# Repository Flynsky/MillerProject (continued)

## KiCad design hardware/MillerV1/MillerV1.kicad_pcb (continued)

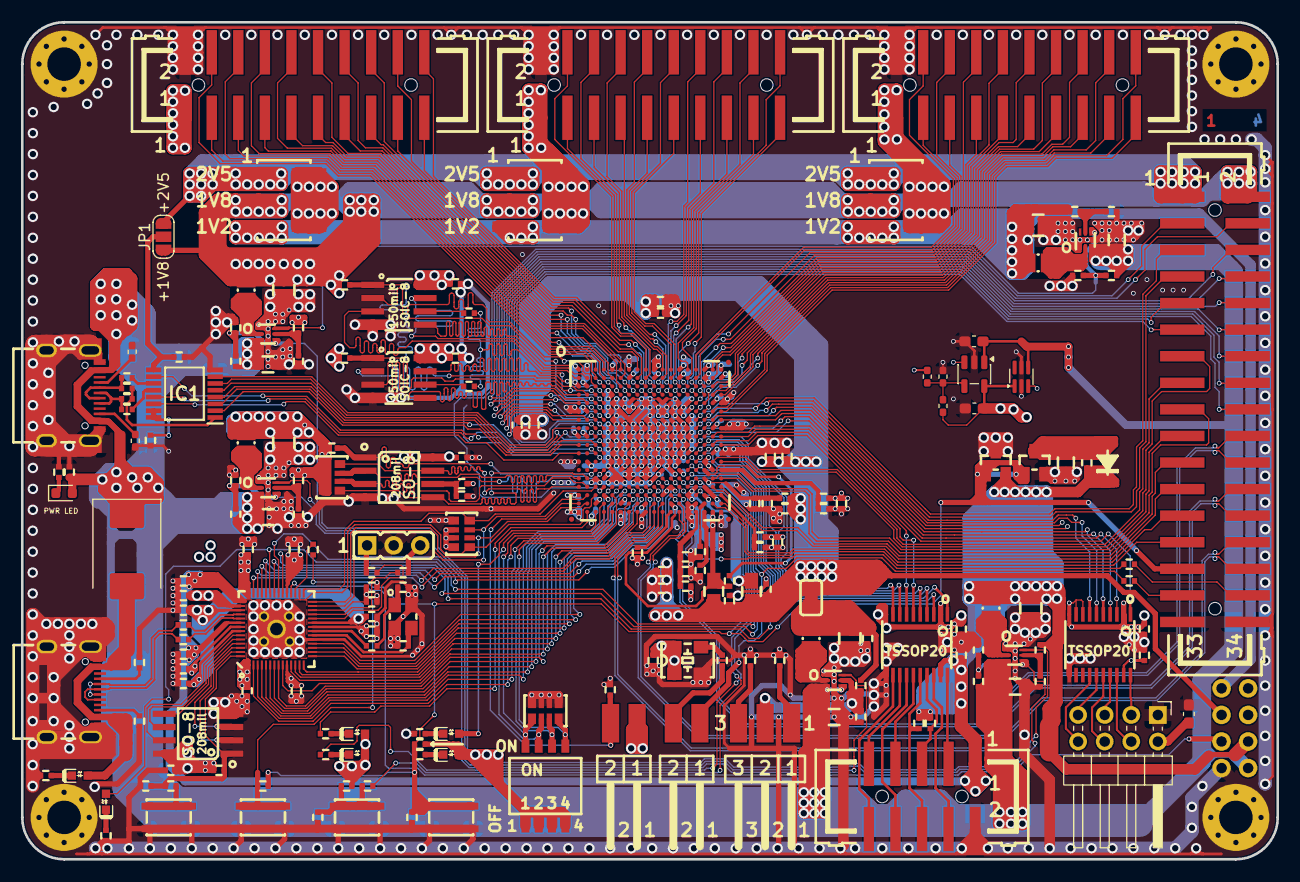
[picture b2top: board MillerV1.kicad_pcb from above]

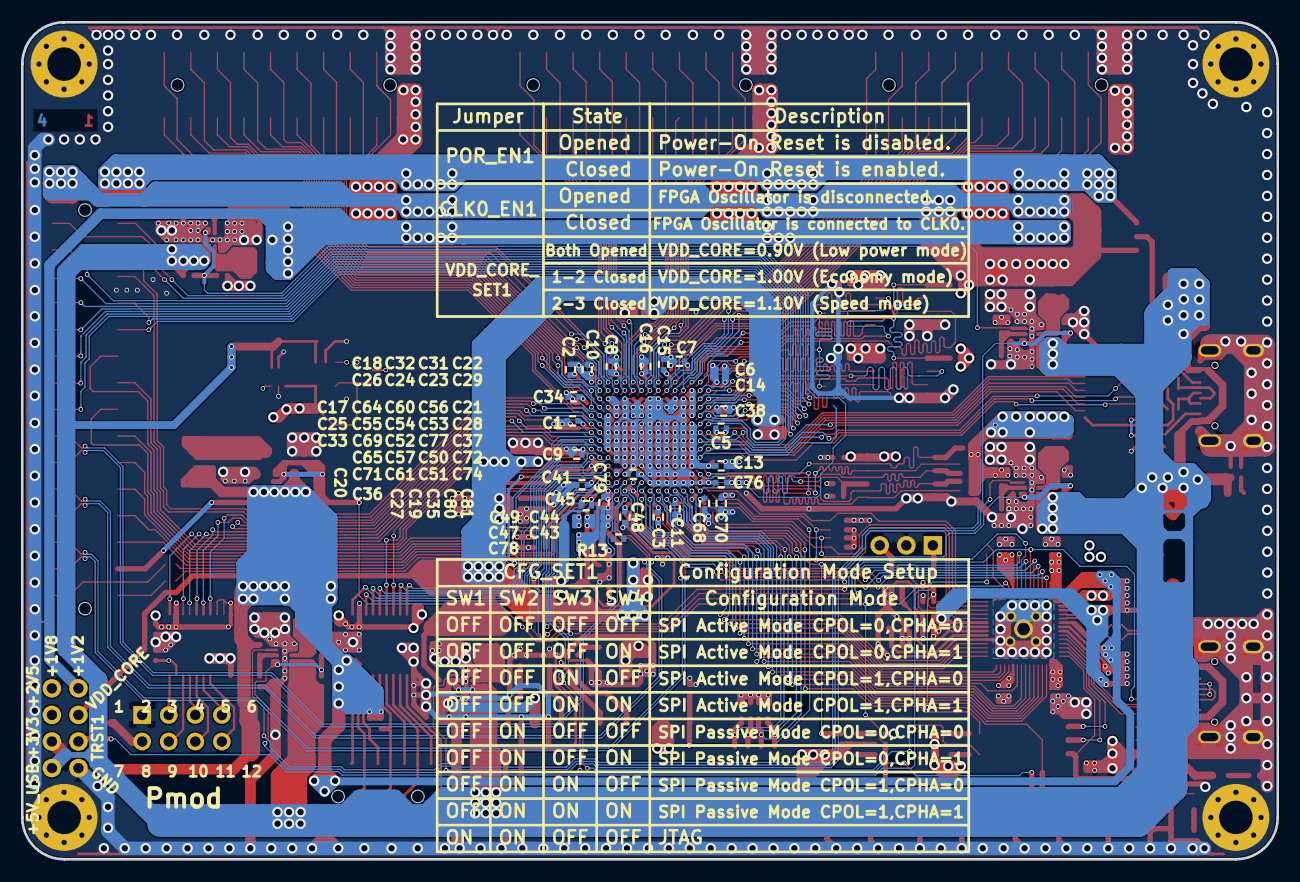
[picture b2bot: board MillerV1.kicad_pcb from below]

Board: 4 copper layers, 120.0 x 80.0 mm, 283 parts (67 on the bottom side), 263 nets.

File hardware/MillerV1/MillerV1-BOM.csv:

"Reference","Qty","Value","DNP","Exclude from BOM","Datasheet","Manufacturer_Part_Number","Mouser Part Number","Mouser Price/Stock","Value 2M","Description"
"BANK_EB1,BANK_NA1,BANK_NB1","3","B-V-20-LF","","","","","","","",""
"BANK_MISC1","1","P-B-V-34-LF","","","","","","","",""
"C1,C2,C3,C4,C5,C6,C7,C8,C43,C47,C58,C62,C66,C68,C73,C78,C106,C107","18","2.2uF/6.3V/20%/X5R/C0402","","","","","","","",""
"C9,C10,C11,C12,C13,C14,C15,C16,C30,C42,C44,C46,C48,C59,C63,C67,C70,C75,C82,C85,C86,C87,C89,C90,C91,C92,C94,C95,C96,C97,C98,C99,C100,C101,C102,C103,C104,C105,C108,C109","40","100nF","","","","","","","",""
"C17,C18,C19,C20,C21,C22,C23,C24,C25,C26,C27,C28,C29,C31,C32,C33,C34,C35,C36,C37,C38,C41,C45,C49,C50,C51,C52,C53,C54,C55,C56,C57,C60,C61,C64,C65,C69,C71,C72,C74,C76,C77,C79,C80,C81","45","1nF/50V/10%/X7R/C0402","","","","","","","",""
"C39,C40,C126","3","10uF","","","","","","","",""
"C83,C112,C114,C118,C120,C124","6","22uF","","","","","","","",""
"C84","1","NA(100nF)","DNP","","","","","","100nF/10V/20%/X5R/C0402",""
"C88","1","22uF","","","","","","","",""
"C93","1","NA/C0402","","","","","","","",""
"C110,C111","2","18pF/50V/5%/C0G/C0402","","","","","","","",""
"C113,C115,C119,C121,C125","5","47uF","","","","","","","",""
"C116,C117,C122,C123","4","NA(2.2uF/6.3V/20%/X5R/C0402)","DNP","","","","","","",""
"C127,C128","2","22uF","DNP","","","","","","",""
"CFG_DONE_LED1,FPGA_LED1","2","LED/GREEN/0603","","","","","","","",""
"CFG_FAILED_LED1,FPGA_RST_LED1,PWR_LED1","3","LED/RED/0603","","","","","","","",""
"CFG_SET1","1","DSHP04TS-S","","","","DSHP04TS-S ","","https://jlcpcb.com/partdetail/XKBConnection-DSHP04TSS/C319050","",""
"CLK0_EN1,POR_EN1","2","H-WX-1x2-LF(Closed)","","","https://m.morethanall.com/images/products/August2018/DCG2AME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","","","","",""
"CR1","1","Q10MHz/30ppm/1.62V-3.63V/4P/5x3.2mm(SX5M10.000M20F30TNN_LCSC-C2901522)","","","","SX5M10.000M20F30TNN","","https://jlcpcb.com/partdetail/3151335-SX5M10000M20F30TNN/C2901522","",""
"D1","1","1N5819S4/SOD123","","","","","","","",""
"FPGA_BUT1,FPGA_RST1,RP-BOOT1,RP-RST1","4","YTS-A016-X","","","","","","","",""
"IC1","1","TUSB1106PWR","","","http://www.ti.com/lit/gpn/tusb1106","TUSB1106PWR","595-TUSB1106PWR","https://www.mouser.co.uk/ProductDetail/Texas-Instruments/TUS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","","Texas Instruments TUSB1106PWR, USB Transceiver, USB 2.0 at 12Mbit/s, 3.3 V, 5 V, 16-Pin TSSOP"
"J2","1","Conn_02x04_Counter_Clockwise","","","","","","","","Generic connector, double row, 02x04, counter clockwise pin numbering scheme (similar to DIP package numbering), script generated (kicad-library-utils/schlib/autogen/connector/)"
"JTAG_LED1","1","LED/YELLOW/0603","","","","","","","",""
"JUMP_CAP1,JUMP_CAP2,JUMP_CAP3,JUMP_CAP4,JUMP_CAP5,JUMP_CAP6","6","MJ6","","","https://store.comet.bg/download-file.php?id=1217","","","","",""
"L1,L2","2","FB0805/600R/2A","","","","","","","",""
"L3,L4,L5,L6,L7","5","1.0uH/4.2A/DCR=35mR/20%/2.00x1.60x1.00mm/L2016(PIM201610-1R0MTS00)","","","","","","","",""
"Q1","1","Q12MHz/20pF/10ppm/4P/3.2x2.5mm","","","","","","","",""
"R1,R4","2","NA(200R/1%/R0402)","DNP","","","","","","",""
"R2,R3,R6,R10","4","0R/R0402","","","","","","","",""
"R5","1","4.7R/R0402","","","","","","","",""
"R7,R17,R18,R25,R26,R27,R66,R76","8","2.2k/R0402","","","","","","","",""
"R8,R19,R28,R45,R53,R57","6","10k/R0402","","","","","","","",""
"R9","1","NA(0R/R0402)","DNP","","","","","","",""
"R11,R12,R13,R15","4","NA(R0402)","DNP","","","","","","",""
"R14,R16,R21,R49","4","NA(10k/R0402)","DNP","","","","","","10k/R0402",""
"R20,R36,R46,R50,R51,R59","6","100R/R0402","","","","","","","",""
"R22","1","200R/1%/R0402","","","","","","","",""
"R23","1","22k","DNP","","","","","","","Resistor, small symbol"
"R24","1","50k","DNP","","","","","","","Resistor, small symbol"
"R29","1","18.2k","DNP","","","","","","","Resistor, small symbol"
"R31,R54,R58","3","22R/R0402","","","","","","","",""
"R47,R48","2","NA(22R/R0402)","DNP","","","","","","",""
"R52","1","NA(100R/R0402)","DNP","","","","","","",""
"R55,R56","2","27R/R0402","","","","","","","",""
"R60","1","3.32k/1%/R0402","","","","","","","",""
"R61","1","4.7k/1%/R0402","","","","","","","",""
"R62,R63,R69,R70","4","100k/R0402","","","","","","","",""
"R64,R65","2","1.05k/1%/R0402","","","","","","","",""
"R67","1","20k/1%/R0402","","","","","","","",""
"R68,R71,R72","3","10k/1%/R0402","","","","","","","",""
"R73","1","1k/1%/R0402","","","","","","","",""
"R74,R75","2","5.1k/1%/R0402","","","","","","","",""
"R77","1","6.04k/1%/R0402","","","","","","","",""
"R78","1","2k/1%/R0402","","","","","","","",""
"R79","1","3.01k/1%/R0402","","","","","","","",""
"RM1,RM2","2","RA1206_(4x0603)_4B8_10k","","","","","","","",""
"RM3","1","NA(RA1206_(4x0603)_4B8_10k)","DNP","","","","","","RA1206_(4x0603)_4B8_10k",""
"SWD1","1","NA(HN1x3)","DNP","","","","","","",""
"U1","1","CCGM1A1(FBGA-324)","","","https://colognechip.com/docs/ds1001-gatemate1-datasheet-2022-05.pdf","CCGM1A1-BGA324","","https://www.digikey.de/de/products/detail/cologne-chip/CCGM1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","",""
"U2","1","HX7027(SOT-23-3)","","","","HX7027","","https://jlcpcb.com/partdetail/HX_hengjiaxing-HX7027/C2984884","",""
"U3","1","NA(ZD25WQ16CSIGT(SOIC-8_208mils))","DNP","","","","","","ZD25WQ16CSIGT(SOIC-8_208mils)",""
"U4","1","NA(MCP120T-300I/TT(SOT-23-3))","DNP","","","","","","",""
"U5,U6","2","TXB0108PWR(TSSOP-20)","","","https://www.ti.com/lit/ds/symlink/txb0108.pdf?ts=17776218025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","TXB0108PWR ","595-TXB0108PWR ","https://www.mouser.de/ProductDetail/Texas-Instruments/TXB010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","",""
"U7,U9","2","LY68S3200SLT(SOIC-8_150mil)","","","LY68S3200SLT.pdf","LY68S3200SLT","","https://jlcpcb.com/partdetail/Lyontek_Inc-LY68S3200SLT/C261882","",""
"U8","1","ZD25WQ16CSIGT(SOIC-8_208mils)","","","","ZD25WQ16CSIGT","","https://www.lcsc.com/product-detail/C5353597.html","",""
"U10","1","RP2040(QFN-56_7x7mm_P0.4mm)","","","https://datasheets.raspberrypi.com/rp2040/rp2040-datasheet.pdf","SC0914(13) ","358-SC091413 ","https://www.mouser.de/ProductDetail/Raspberry-Pi/SC091413?qs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","",""
"U11,U12,U13,U14,U15","5","TPS62A02ADRLR(SOT-563-6)","","","https://www.ti.com/lit/ds/symlink/tps62a02a.pdf?ts=170966717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","TPS62A02ADRLR","595-TPS62A02ADRLR ","https://www.mouser.de/ProductDetail/Texas-Instruments/TPS62A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","",""
"U16","1","TLV75801PDBV","DNP","","https://www.ti.com/lit/ds/symlink/tlv758p.pdf","TLV75801PDBVR","595-TLV75801PDBVR ","https://www.mouser.de/ProductDetail/Texas-Instruments/TLV758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","","500mA Low-Dropout Linear Regulator, Adjustable Output, SOT-23-5"
"U18","1","SiP32432DR3","DNP","","http://www.vishay.com.hk/docs/66597/sip32431.pdf","SIP32432DR3-T1GE3 ","78-SIP32432DR3-T1GE3 ","https://www.mouser.de/ProductDetail/Vishay-Semiconductors/SI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","","10 pA, Ultra Low Leakage and Quiescent Current, Load Switch with Reverse Blocking, Low Enable, SC-70-6"
"UEXT1","1","P-B-V-10-LF","","","","","","","",""
"USB-C1","1","USB-C-16P-F(A40-00119-A52-12)","","","https://gct.co/connector/usb4105","","","","",""
"VDD_CORE_E1","1","Closed","DNP","","","","","","",""
"VDD_CORE_SET1","1","H-WX-1x3-LF(1-2:Closed/2-3:Opened)","","","https://m.morethanall.com/images/products/August2018/DCG2AME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","","","","",""
"VDD_EB_SEL1,VDD_NA_SEL1,VDD_NB_SEL1","3","H-V33X-2x03-LF(1-2:Closed)","","","","","","","",""

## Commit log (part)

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2026-03-30 added Olimex hard and softare, reformed schemaktic to make human readable
2026-04-07 Added git ignore file
2026-04-07 sys_verilog_test folder with Makefile for some flash tests for the olimex board
2026-04-22 made room for tobi
2026-04-28 added VCC siwtcher for ISO Interface
2026-05-02 TUSB hinzugefügt muss aber noch gerouted werden
2026-05-02 KiCad Änderungen - Zwischenstand
2026-05-04 merged USB PHY
2026-05-04 added BOM and pinlist
2026-05-09 assigned FPGA pins to USB PHY
2026-05-12 added graphics
2026-05-12 added
2026-05-15 Updated BOM(now seperate Folder)
2026-05-17 Alles Kapput mach das neu in MAIN
2026-05-17 History in gitignore
2026-05-17 kleine Änderungen und GND
2026-05-18 fixed scematic/pcb differences
2026-05-21 Update PCB footprints and USB power nets
    Modify MillerV1.kicad_pcb: fix USB power net assignments and clean up footprints. Several USB VBUS pads were retargeted from +5V_USB (and +5V_USB_2) to the correct nets (Net-(D3-A) or +5V_USB). Added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
2026-05-22 sollte soweit fertig sein
2026-05-22 solved some DRC issues
2026-05-22 solved some DRC issues, downgraded from nightly to standard kicad yeay
2026-06-01 minor changes
